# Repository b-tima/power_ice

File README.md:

# power_ice

Project files created for the course II2302 Sensor Based Systems @KTH.

## Project members:

* Morgan Adamsson
* Samuel Svensson
* Skander Ben Messaoud
* Robin Carlet

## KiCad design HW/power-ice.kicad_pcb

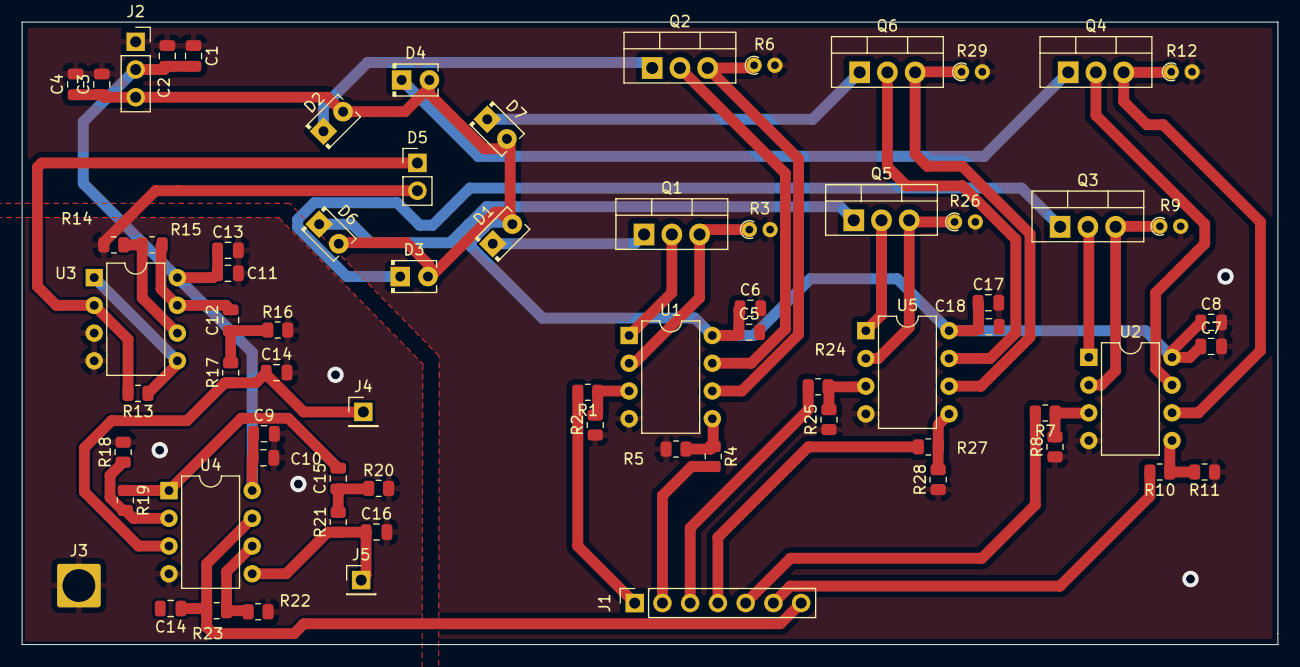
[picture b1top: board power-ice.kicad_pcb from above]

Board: 2 copper layers, 115.0 x 57.0 mm, 71 parts (0 on the bottom side), 46 nets.

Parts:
C1, C2, C3, C4, C5, C6, C7, C8, C9, C10, C11, C12, C13, C14, C14#2, C15, C16, C17, C18: C; C_0805_2012Metric
D1, D2, D3, D4, D6, D7: LED; LED_D2.0mm_W4.0mm_H2.8mm_FlatTop
D5: D_Photo; PinHeader_1x02_P2.54mm_Vertical
J1: Conn_01x07_Female; PinSocket_1x07_P2.54mm_Vertical
J2: Conn_01x03_Female; PinSocket_1x03_P2.54mm_Vertical
J3: Conn_01x01_Female; SolderWire-2.5sqmm_1x01_D2.4mm_OD3.6mm
J4, J5: Conn_01x01_Female; PinHeader_1x01_P2.54mm_Vertical
Q1, Q2, Q3, Q4, Q5, Q6: Q_NMOS_DGS; TO-220-3_Vertical
R1, R4, R7, R10, R24, R27: 18k; R_0805_2012Metric
R2, R5, R8, R11, R25, R28: 10k; R_0805_2012Metric
R3, R6, R9, R12, R26, R29: 15; R_Axial_DIN0204_L3.6mm_D1.6mm_P1.90mm_Vertical
R13, R14, R15, R16, R17, R18, R19, R20, R21, R22, R23: R; R_0805_2012Metric
U1, U2, U3, U4, U5: MCP6002-xP; DIP-8_W7.62mm

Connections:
+3V3: C1.2, C2.1, C9.1, C10.1, C11.1, C13.1, J2.2, U3.8 (V+), U4.8 (V+)
+5V: C3.1, C4.1, C5.1, C6.1, C7.1, C8.1, C17.1, C18.1, D1.2 (A), D2.2 (A), D3.2 (A), D4.2 (A), D6.2 (A), D7.2 (A), J2.3
/IR_LED/InputLedAblock: J1.1, R1.2
/IR_LED/InputLedBblock: J1.2, R4.2
/Sheet6239F98A/OutputPDCircuit: C14#2.1, J1.7, R23.1, U4.7
/sheet6238A8B8/InputLedAblock: J1.3, R24.2
/sheet6238A8B8/InputLedBblock: J1.4, R27.2
/sheet62353F20/InputLedAblock: J1.5, R7.2
/sheet62353F20/InputLedBblock: J1.6, R10.2
GND: C1.1, C2.2, C3.2, C4.2, C5.2, C6.2, C7.2, C8.2, C17.2, C18.2, J2.1, R2.1, R3.2, R5.1, R6.2, R8.1, R9.2, R11.1, R12.2, R25.1, R26.2, R28.1, R29.2, U1.4 (V-), U2.4 (V-), U5.4 (V-)
GNDA: C9.2, C10.2, C11.2, C13.2, C14.2, C16.2, D5.2 (A), J3.1, R14.2, R16.2, R18.2, R20.2, R22.2, U3.3 (+), U3.4 (V-), U4.4 (V-)
unnamed: C12.1, R16.1, R17.2
unnamed: C12.2, R15.1, U3.7
unnamed: C14.1, J4.1, R17.1, U4.3 (+)
unnamed: C15.1, R20.1, R21.2
unnamed: C15.2, R19.1, U4.1
unnamed: C16.1, J5.1, R21.1, U4.5 (+)
unnamed: D1.1 (K), Q1.1 (D)
unnamed: D2.1 (K), Q2.1 (D)
unnamed: D3.1 (K), Q3.1 (D)
unnamed: D4.1 (K), Q4.1 (D)
unnamed: D5.1 (K), R13.2, U3.2 (-)
unnamed: D6.1 (K), Q5.1 (D)
unnamed: D7.1 (K), Q6.1 (D)
unnamed: Q1.2 (G), U1.1
unnamed: Q1.3 (S), R3.1, U1.2 (-)
unnamed: Q2.2 (G), U1.7
unnamed: Q2.3 (S), R6.1, U1.6 (-)
unnamed: Q3.2 (G), U2.1
unnamed: Q3.3 (S), R9.1, U2.2 (-)
unnamed: Q4.2 (G), U2.7
unnamed: Q4.3 (S), R12.1, U2.6 (-)
unnamed: Q5.2 (G), U5.1
unnamed: Q5.3 (S), R26.1, U5.2 (-)
unnamed: Q6.2 (G), U5.7
unnamed: Q6.3 (S), R29.1, U5.6 (-)
unnamed: R1.1, R2.2, U1.3 (+)
unnamed: R4.1, R5.2, U1.5 (+)
unnamed: R7.1, R8.2, U2.3 (+)
unnamed: R10.1, R11.2, U2.5 (+)
unnamed: R13.1, U3.1, U3.5 (+)
unnamed: R14.1, R15.2, U3.6 (-)
unnamed: R18.1, R19.2, U4.2 (-)
unnamed: R22.1, R23.2, U4.6 (-)
unnamed: R24.1, R25.2, U5.3 (+)
unnamed: R27.1, R28.2, U5.5 (+)

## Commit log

2022-03-12 added hw files
2022-03-12 added software
2022-03-12 added data and matlab files
2022-03-12 added readme
2022-03-14 added data
2022-03-16 added presentation
2022-03-22 added report
2022-03-22 deleted .vscode files
